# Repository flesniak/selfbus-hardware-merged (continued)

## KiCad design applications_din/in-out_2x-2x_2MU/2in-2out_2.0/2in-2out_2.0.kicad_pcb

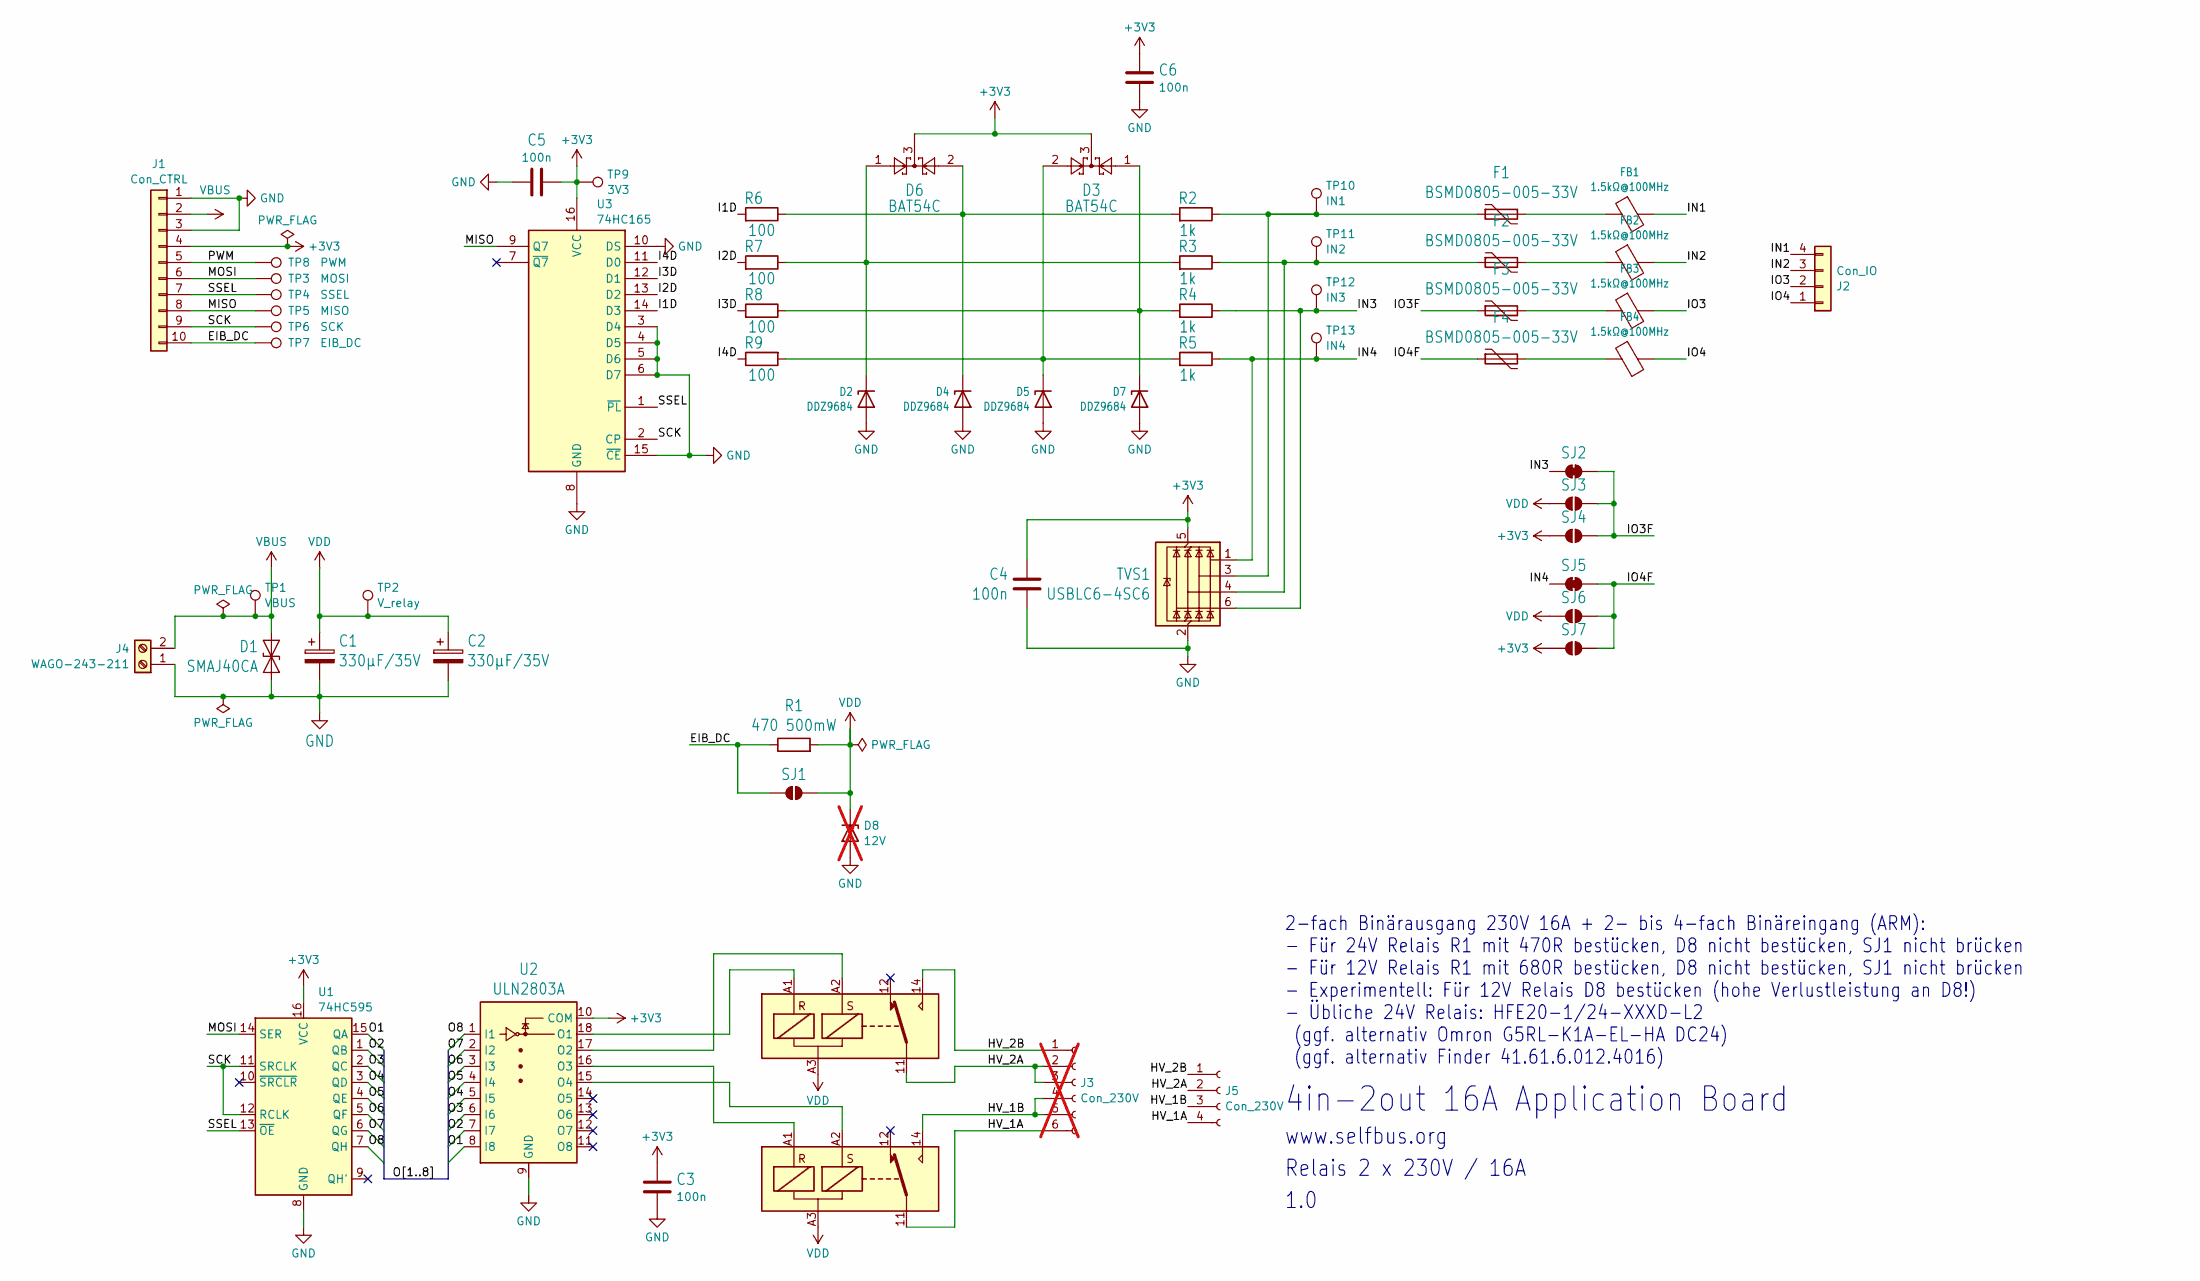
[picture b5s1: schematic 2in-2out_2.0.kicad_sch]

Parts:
C1, C2: 330µF/35V; CP_Radial_D8.0mm_P3.50mm
C3, C4, C5, C6: 100n; C_0805_2012Metric
D1: SMAJ40CA; D_SMA
D2, D4, D5, D7: DDZ9684; D_SOD-123
D3, D6: BAT54C; SOT-23
D8: 12V; D_MiniMELF; not fitted
F1, F2, F3, F4: BSMD0805-005-33V; Fuse_0805_2012Metric
FB1, FB2, FB3, FB4: 1.5kΩ@100MHz; L_0805_2012Metric
J1: Con_CTRL; Molex_KK-254_AE-6410-10A_1x10_P2.54mm_Vertical
J2: Con_IO; TerminalBlock_Phoenix_PTSM-0,5-4-2.5-H-THR_1x04_P2.50mm_Hor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
J3: Con_230V; TerminalBlock_Phoenix_MKDS-3-6-5.08_1x06_P5.08mm_Horizontal; not fitted
J4: WAGO-243-211; W243-211_1x02_P5.75
J5: Con_230V; TerminalBlock_MetzConnect_Type701_RT11L03HGLU_1x04_P6.35mm_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
K1, K2: HFE20-1/24-1HSD-L2; HFE20-GENERIC-COMBO
R1: 470 500mW; R_1206_3216Metric
R2, R3, R4, R5: 1k; R_0805_2012Metric
R6, R7, R8, R9: 100; R_0805_2012Metric
SJ1: RELAY_24V; SolderJumper-2_P1.3mm_Open_Pad1.0x1.5mm
SJ2: IN3_INPUT; SolderJumper-2_P1.3mm_Open_Pad1.0x1.5mm
SJ3: IN3_VDD; SolderJumper-2_P1.3mm_Open_Pad1.0x1.5mm
SJ4: IN3_3V3; SolderJumper-2_P1.3mm_Open_Pad1.0x1.5mm
SJ5: IN4_INPUT; SolderJumper-2_P1.3mm_Open_Pad1.0x1.5mm
SJ6: IN4_VDD; SolderJumper-2_P1.3mm_Open_Pad1.0x1.5mm
SJ7: IN4_3V3; SolderJumper-2_P1.3mm_Open_Pad1.0x1.5mm
TP1: VBUS; TestPoint_Pad_D1.5mm
TP2: V_relay; TestPoint_Pad_D1.5mm
TP3: MOSI; TestPoint_Pad_D1.5mm
TP4: SSEL; TestPoint_Pad_D1.5mm
TP5: MISO; TestPoint_Pad_D1.5mm
TP6: SCK; TestPoint_Pad_D1.5mm
TP7: EIB_DC; TestPoint_Pad_D1.5mm
TP8: PWM; TestPoint_Pad_D1.5mm
TP9: 3V3; TestPoint_Pad_D1.5mm
TP10: IN1; TestPoint_Pad_D1.0mm
TP11: IN2; TestPoint_Pad_D1.0mm
TP12: IN3; TestPoint_Pad_D1.0mm
TP13: IN4; TestPoint_Pad_D1.0mm
TVS1: USBLC6-4SC6; SOT-23-6
U1: 74HC595; SOIC-16_3.9x9.9mm_P1.27mm
U2: ULN2803A; SOIC-18W_7.5x11.6mm_P1.27mm
U3: 74HC165; SO-16_3.9x9.9mm_P1.27mm

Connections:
+3V3: C3.1, C4.2, C5.1, C6.1, D3.3, D6.3, J1.4, SJ4.1 (A), SJ7.1 (A), TP9.1, TVS1.5 (VBUS), U1.16 (VCC), U2.10 (COM), U3.16 (VCC)
/EIB_DC: J1.10, R1.1, SJ1.1 (A), TP7.1
/HV_1A: J3.6, J5.4, K1.11
/HV_1B: J3.4, J3.5, J5.3, K1.14
/HV_2A: J3.2, J3.3, J5.2, K2.11
/HV_2B: J3.1, J5.1, K2.14
/I1D: R6.2, U3.14 (D3)
/I2D: R7.2, U3.13 (D2)
/I3D: R8.2, U3.12 (D1)
/I4D: R9.1, U3.11 (D0)
/IN1: FB1.2, J2.4
/IN2: FB2.2, J2.3
/IN3: R4.1, SJ2.1 (A), TP12.1, TVS1.6 (I/O4)
/IN4: R5.1, SJ5.1 (A), TP13.1, TVS1.1 (I/O1)
/IO3: FB3.2, J2.2
/IO3F: F3.1, SJ2.2 (B), SJ3.2 (B), SJ4.2 (B)
/IO4: FB4.2, J2.1
/IO4F: F4.1, SJ5.2 (B), SJ6.2 (B), SJ7.2 (B)
/MISO: J1.8, TP5.1, U3.9 (Q7)
/MOSI: J1.6, TP3.1, U1.14 (SER)
/O1: U1.15 (QA), U2.8 (I8)
/O2: U1.1 (QB), U2.7 (I7)
/O3: U1.2 (QC), U2.6 (I6)
/O4: U1.3 (QD), U2.5 (I5)
/O5: U1.4 (QE), U2.4 (I4)
/O6: U1.5 (QF), U2.3 (I3)
/O7: U1.6 (QG), U2.2 (I2)
/O8: U1.7 (QH), U2.1 (I1)
/PWM: J1.5, TP8.1
/SCK: J1.9, TP6.1, U1.11 (SRCLK), U1.12 (RCLK), U3.2 (CP)
/SSEL: J1.7, TP4.1, U1.13 (~OE), U3.1 (~PL)
GND: C1.2, C2.2, C3.2, C4.1, C5.2, C6.2, D1.1 (A1), D2.2 (A), D4.2 (A), D5.2 (A), D7.2 (A), D8.2 (A), J1.1, J1.3, J4.1, TVS1.2 (GND), U1.8 (GND), U2.9 (GND), U3.3 (D4), U3.4 (D5), U3.5 (D6), U3.6 (D7), U3.8 (GND), U3.10 (DS), U3.15 (~CE)
unnamed: D2.1 (K), D6.1, R3.2, R7.1
unnamed: D4.1 (K), D6.2, R2.2, R6.1
unnamed: D3.2, D5.1 (K), R5.2, R9.2
unnamed: D3.1, D7.1 (K), R4.2, R8.1
unnamed: F1.2, FB1.1
unnamed: F2.2, FB2.1
unnamed: F3.2, FB3.1
unnamed: F4.2, FB4.1
unnamed: F1.1, R2.1, TP10.1, TVS1.3 (I/O2)
unnamed: F2.1, R3.1, TP11.1, TVS1.4 (I/O3)
unnamed: K2.A1, U2.18 (O1)
unnamed: K2.A2, U2.17 (O2)
unnamed: K1.A1, U2.16 (O3)
unnamed: K1.A2, U2.15 (O4)
VBUS: D1.2 (A2), J1.2, J4.2, TP1.1
VDD: C1.1, C2.1, D8.1 (K), K1.A3, K2.A3, R1.2, SJ1.2 (B), SJ3.1 (A), SJ6.1 (A), TP2.1

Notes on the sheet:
www.selfbus.org
4in-2out 16A Application Board
1.0
2-fach Binärausgang 230V 16A + 2- bis 4-fach Binäreingang (ARM): - Für 24V Relais R1 mit 470R bestücken, D8 nicht bestücken, SJ1 nicht brücken - Für 12V Relais R1 mit 680R bestücken, D8 nicht bestücken, SJ1 nicht brücken - Experimentell: Für 12V Relais D8 bestücken (hohe Verlustleistung an D8!) - Ü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
Relais 2 x 230V / 16A

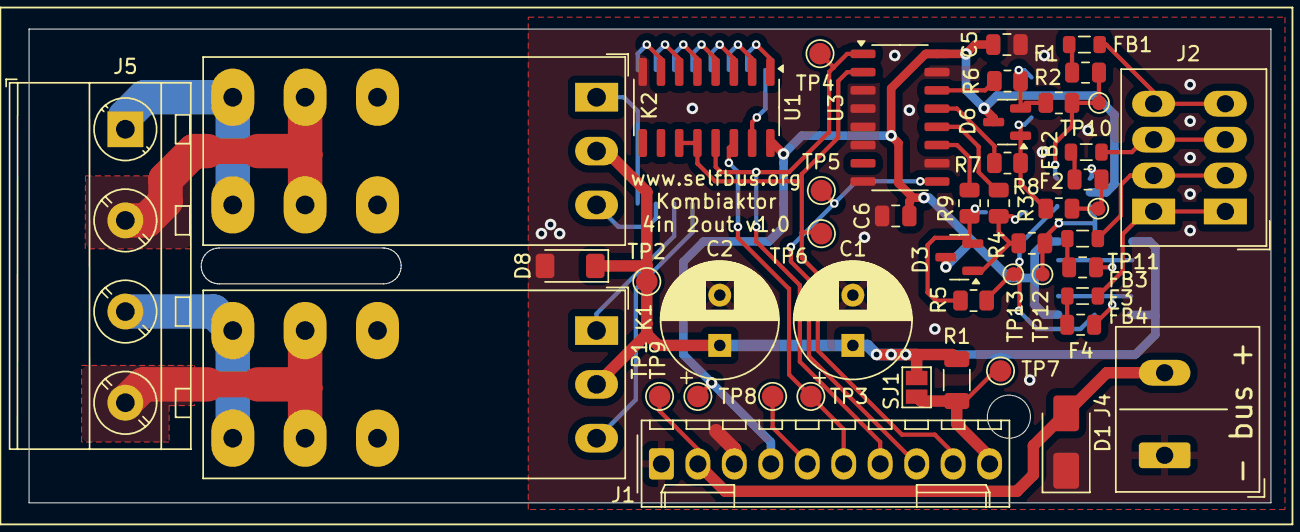
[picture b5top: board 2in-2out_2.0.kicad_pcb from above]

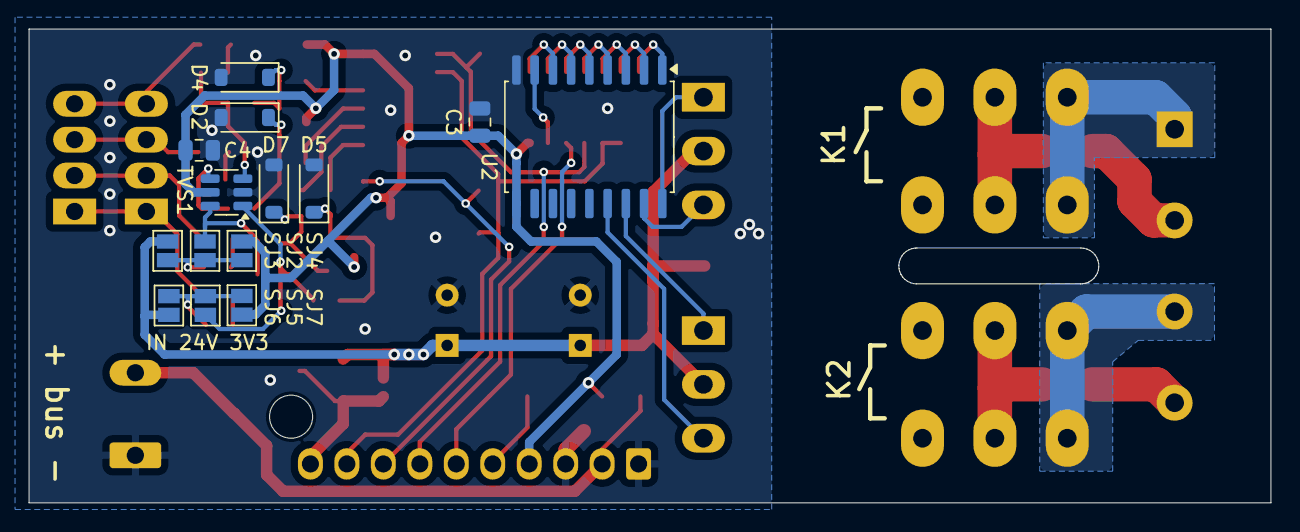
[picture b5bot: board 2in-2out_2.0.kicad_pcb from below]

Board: 2 copper layers, 86.5 x 33.0 mm, 62 parts (14 on the bottom side), 48 nets.

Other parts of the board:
HUT_CNMB_2: BOT; HUT_CNMB_2

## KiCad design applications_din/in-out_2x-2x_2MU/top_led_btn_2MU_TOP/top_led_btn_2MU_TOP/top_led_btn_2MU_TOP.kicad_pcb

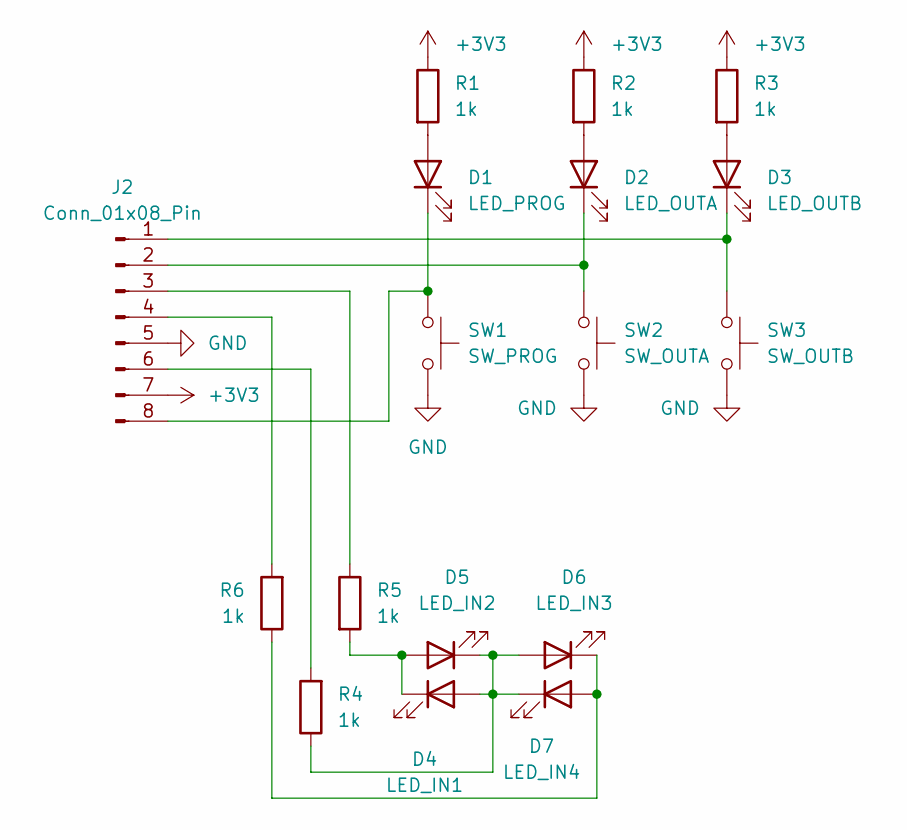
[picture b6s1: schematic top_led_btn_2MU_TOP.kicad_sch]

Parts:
D1: LED_PROG; LED_0805_2012Metric
D2: LED_OUTA; LED_0805_2012Metric
D3: LED_OUTB; LED_0805_2012Metric
D4: LED_IN1; LED_0805_2012Metric
D5: LED_IN2; LED_0805_2012Metric
D6: LED_IN3; LED_0805_2012Metric
D7: LED_IN4; LED_0805_2012Metric
J2: Conn_01x08_Pin; PinHeader_1x08_P2.54mm_Vertical
R1, R2, R3, R4, R5, R6: 1k; R_0805_2012Metric
SW1: SW_PROG; SW_SPST_Omron_B3FS-100xP
SW2: SW_OUTA; SW_SPST_Omron_B3FS-100xP
SW3: SW_OUTB; SW_SPST_Omron_B3FS-100xP

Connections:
+3V3: J2.7, R1.1, R2.1, R3.1
GND: J2.5, SW1.1, SW2.1, SW3.1
unnamed: D1.2 (A), R1.2
unnamed: D1.1 (K), J2.8, SW1.2
unnamed: D2.2 (A), R2.2
unnamed: D2.1 (K), J2.2, SW2.2
unnamed: D3.2 (A), R3.2
unnamed: D3.1 (K), J2.1, SW3.2
unnamed: D4.2 (A), D5.1 (K), D6.2 (A), D7.1 (K), R4.1
unnamed: D4.1 (K), D5.2 (A), R5.2
unnamed: D6.1 (K), D7.2 (A), R6.1
unnamed: J2.3, R5.1
unnamed: J2.4, R6.2
unnamed: J2.6, R4.2

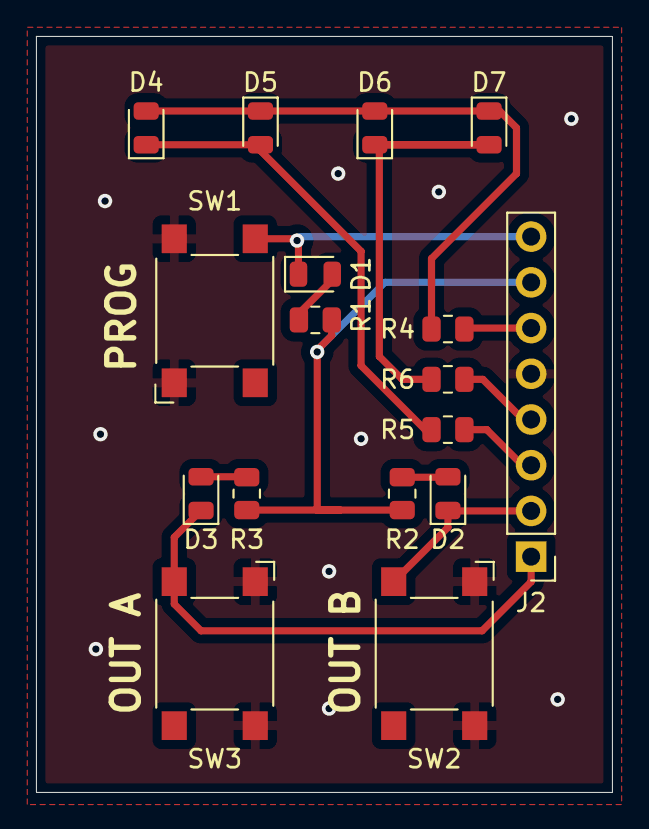
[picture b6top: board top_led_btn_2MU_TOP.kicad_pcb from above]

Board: 2 copper layers, 32.0 x 42.0 mm, 17 parts (0 on the bottom side), 14 nets.

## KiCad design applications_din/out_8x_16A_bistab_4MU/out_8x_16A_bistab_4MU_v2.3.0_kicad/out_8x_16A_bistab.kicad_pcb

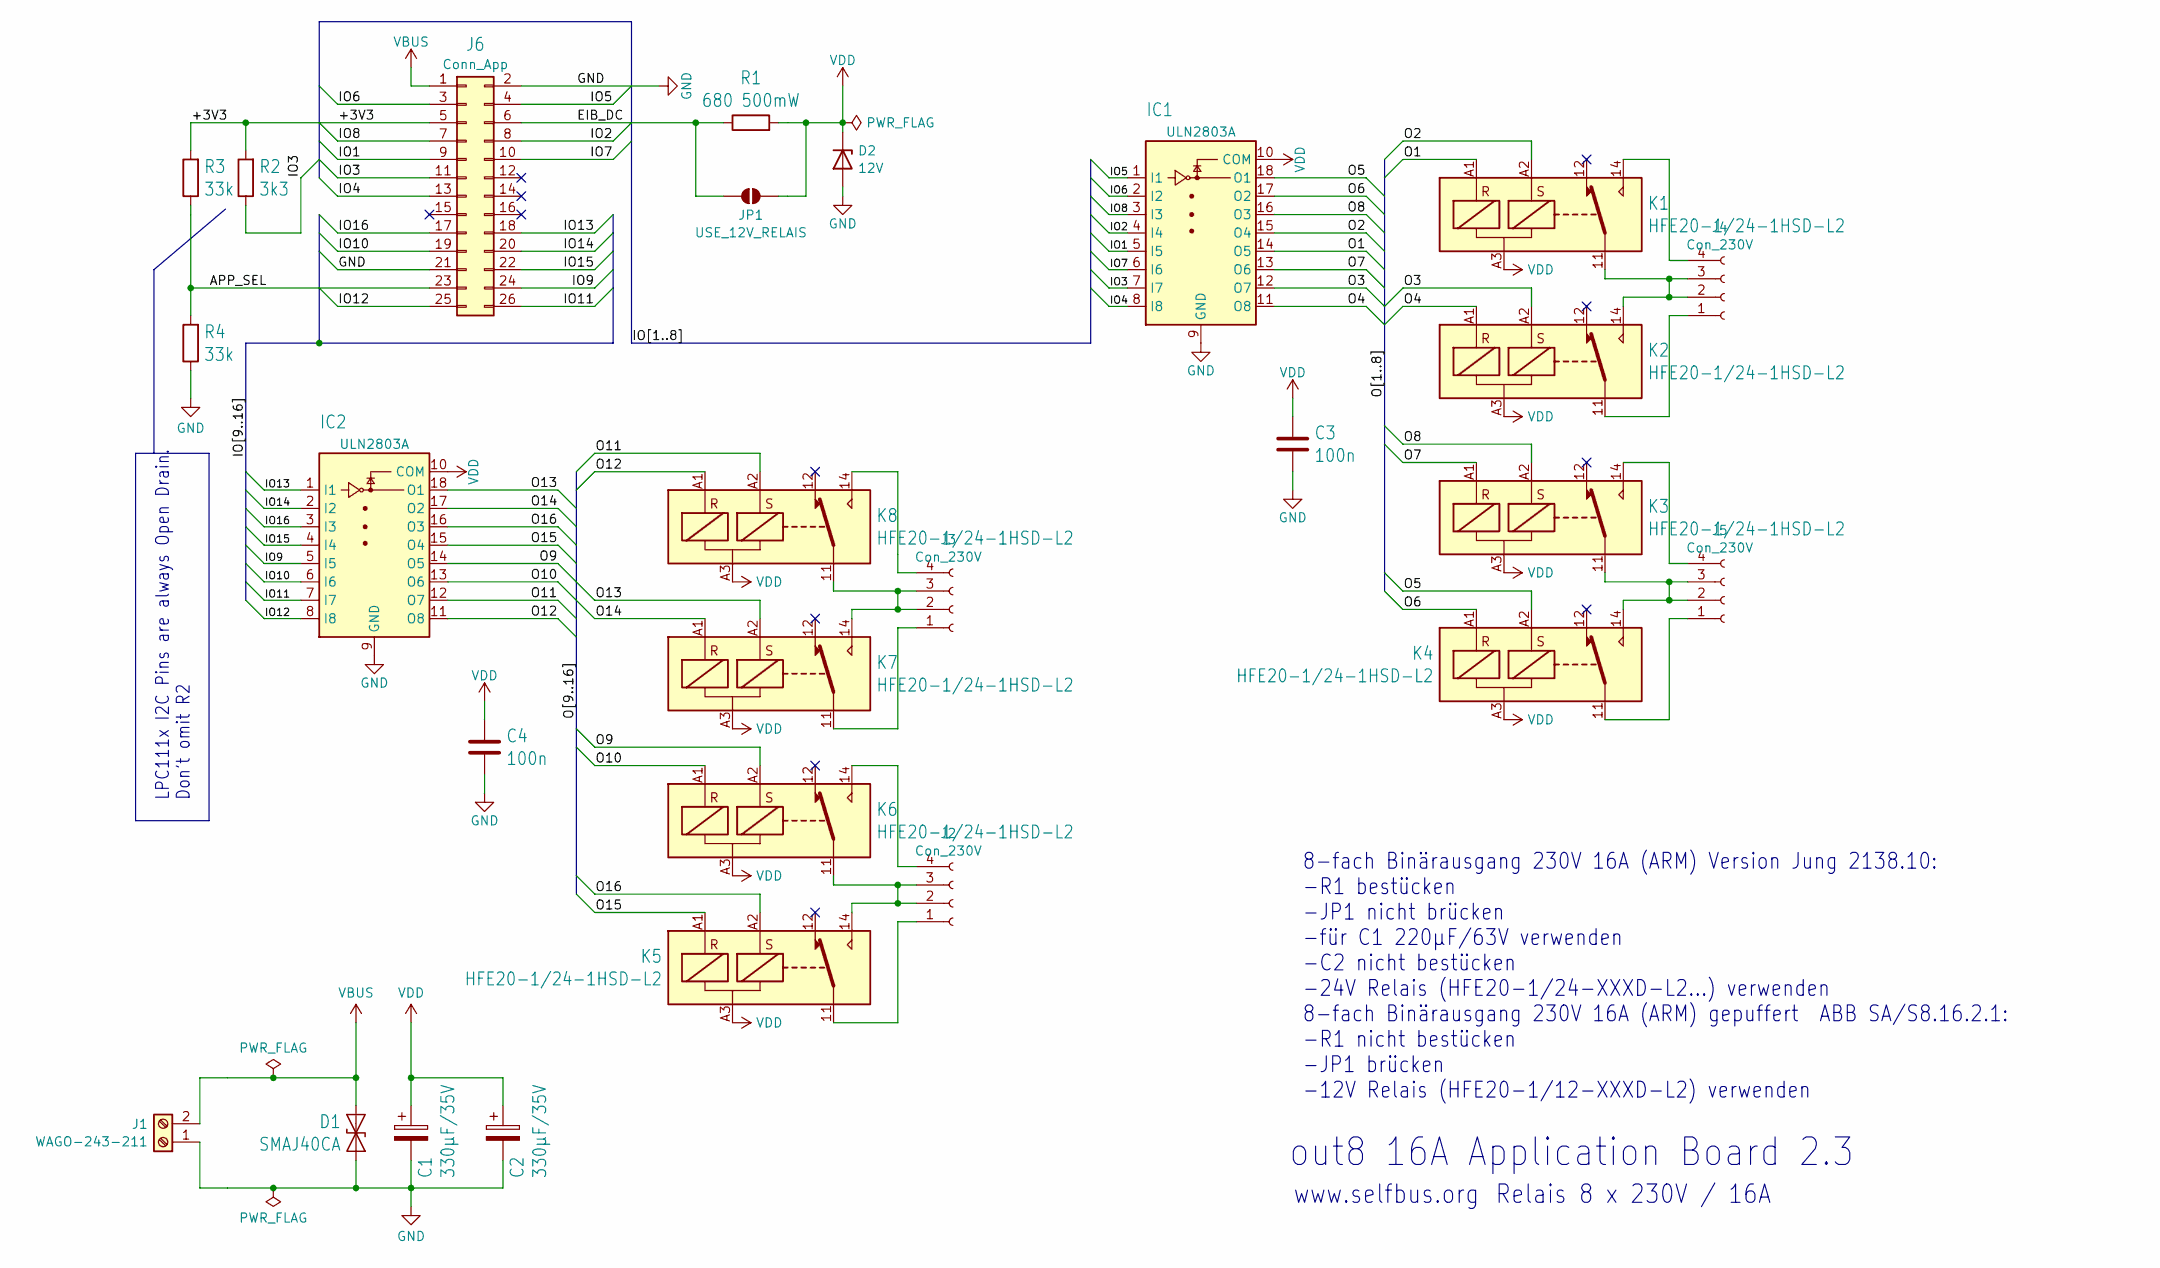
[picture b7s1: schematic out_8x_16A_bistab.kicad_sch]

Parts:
C1, C2: 330µF/35V; CP_Radial_D8.0mm_P3.50mm
C3, C4: 100n; C_0805_2012Metric
D1: SMAJ40CA; D_SMA
D2: 12V; D_MiniMELF
IC1, IC2: ULN2803A; SOIC-18W_7.5x11.6mm_P1.27mm
J1: WAGO-243-211; W243-211_1x02_P5.75
J2, J3, J4, J5: Con_230V; Altech_AK100_1x04_P5.00mm
J6: Conn_App; IDC-Header_2x13_P2.54mm_Vertical_SMD
JP1: USE_12V_RELAIS; SolderJumper-2_P1.3mm_Open_Pad1.0x1.5mm
K1, K2, K3, K4, K5, K6, K7, K8: HFE20-1/24-1HSD-L2; HFE20-1-L2
R1: 680 500mW; R_1206_3216Metric
R2: 3k3; R_0805_2012Metric
R3, R4: 33k; R_0805_2012Metric

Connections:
/+3V3: J6.5, R2.2, R3.2
/APP_SEL: J6.23, R3.1, R4.2
/EIB_DC: J6.6, JP1.1 (A), R1.1
/IO1: IC1.5 (I5), J6.9
/IO2: IC1.4 (I4), J6.8
/IO3: IC1.7 (I7), J6.11, R2.1
/IO4: IC1.8 (I8), J6.13
/IO5: IC1.1 (I1), J6.4
/IO6: IC1.2 (I2), J6.3
/IO7: IC1.6 (I6), J6.10
/IO8: IC1.3 (I3), J6.7
/IO9: IC2.5 (I5), J6.24
/IO10: IC2.6 (I6), J6.19
/IO11: IC2.7 (I7), J6.26
/IO12: IC2.8 (I8), J6.25
/IO13: IC2.1 (I1), J6.18
/IO14: IC2.2 (I2), J6.20
/IO15: IC2.4 (I4), J6.22
/IO16: IC2.3 (I3), J6.17
/O1: IC1.14 (O5), K1.A1
/O2: IC1.15 (O4), K1.A2
/O3: IC1.12 (O7), K2.A2
/O4: IC1.11 (O8), K2.A1
/O5: IC1.18 (O1), K4.A2
/O6: IC1.17 (O2), K4.A1
/O7: IC1.13 (O6), K3.A1
/O8: IC1.16 (O3), K3.A2
/O9: IC2.14 (O5), K6.A2
/O10: IC2.13 (O6), K6.A1
/O11: IC2.12 (O7), K8.A2
/O12: IC2.11 (O8), K8.A1
/O13: IC2.18 (O1), K7.A2
/O14: IC2.17 (O2), K7.A1
/O15: IC2.15 (O4), K5.A1
/O16: IC2.16 (O3), K5.A2
GND: C1.2, C2.2, C3.2, C4.2, D1.1 (A1), D2.2 (A), IC1.9 (GND), IC2.9 (GND), J1.1, J6.2, J6.21, R4.1
unnamed: J2.1, K5.11
unnamed: J2.2, J2.3, K5.14, K6.11
unnamed: J2.4, K6.14
unnamed: J3.1, K7.11
unnamed: J3.2, J3.3, K7.14, K8.11
unnamed: J3.4, K8.14
unnamed: J4.1, K2.11
unnamed: J4.2, J4.3, K1.11, K2.14
unnamed: J4.4, K1.14
unnamed: J5.1, K4.11
unnamed: J5.2, J5.3, K3.11, K4.14
unnamed: J5.4, K3.14
VBUS: D1.2 (A2), J1.2, J6.1
VDD: C1.1, C2.1, C3.1, C4.1, D2.1 (K), IC1.10 (COM), IC2.10 (COM), JP1.2 (B), K1.A3, K2.A3, K3.A3, K4.A3, K5.A3, K6.A3, K7.A3, K8.A3, R1.2

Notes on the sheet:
www.selfbus.org
out8 16A Application Board 2.3
8-fach Binärausgang 230V 16A (ARM) Version Jung 2138.10: -R1 bestücken -JP1 nicht brücken -für C1 220µF/63V verwenden -C2 nicht bestücken -24V Relais (HFE20-1/24-XXXD-L2...) verwenden 8-fach Binärausgang 230V 16A (ARM) gepuffert ABB SA/S8.16.2.1: -R1 nicht bestücken -JP1 brücken -12V Relais (HFE20-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
Relais 8 x 230V / 16A
LPC111x I2C Pins are always Open Drain. Don't omit R2~{}

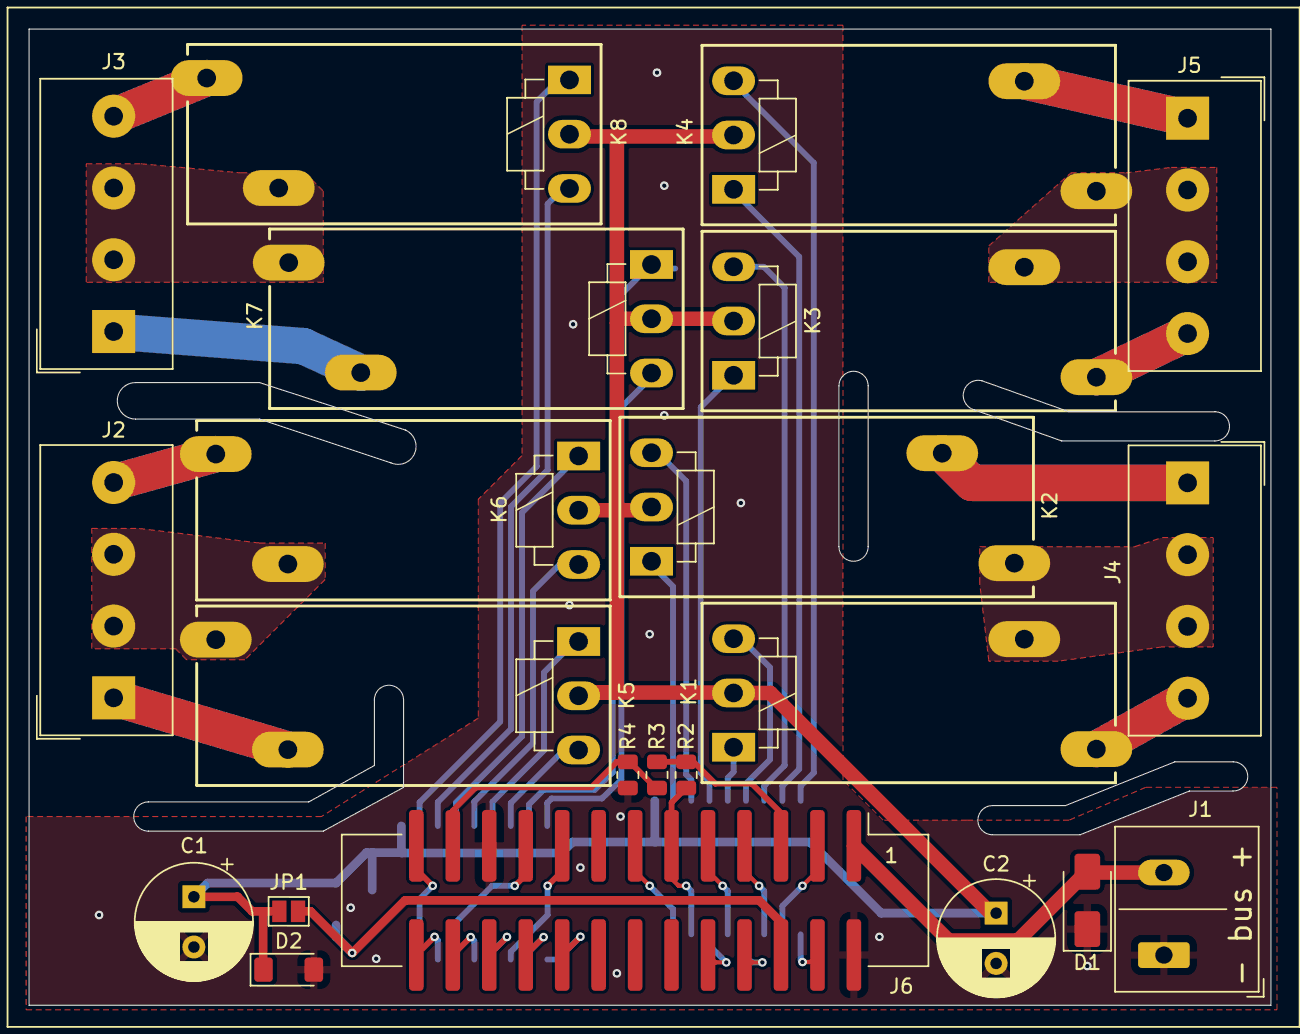
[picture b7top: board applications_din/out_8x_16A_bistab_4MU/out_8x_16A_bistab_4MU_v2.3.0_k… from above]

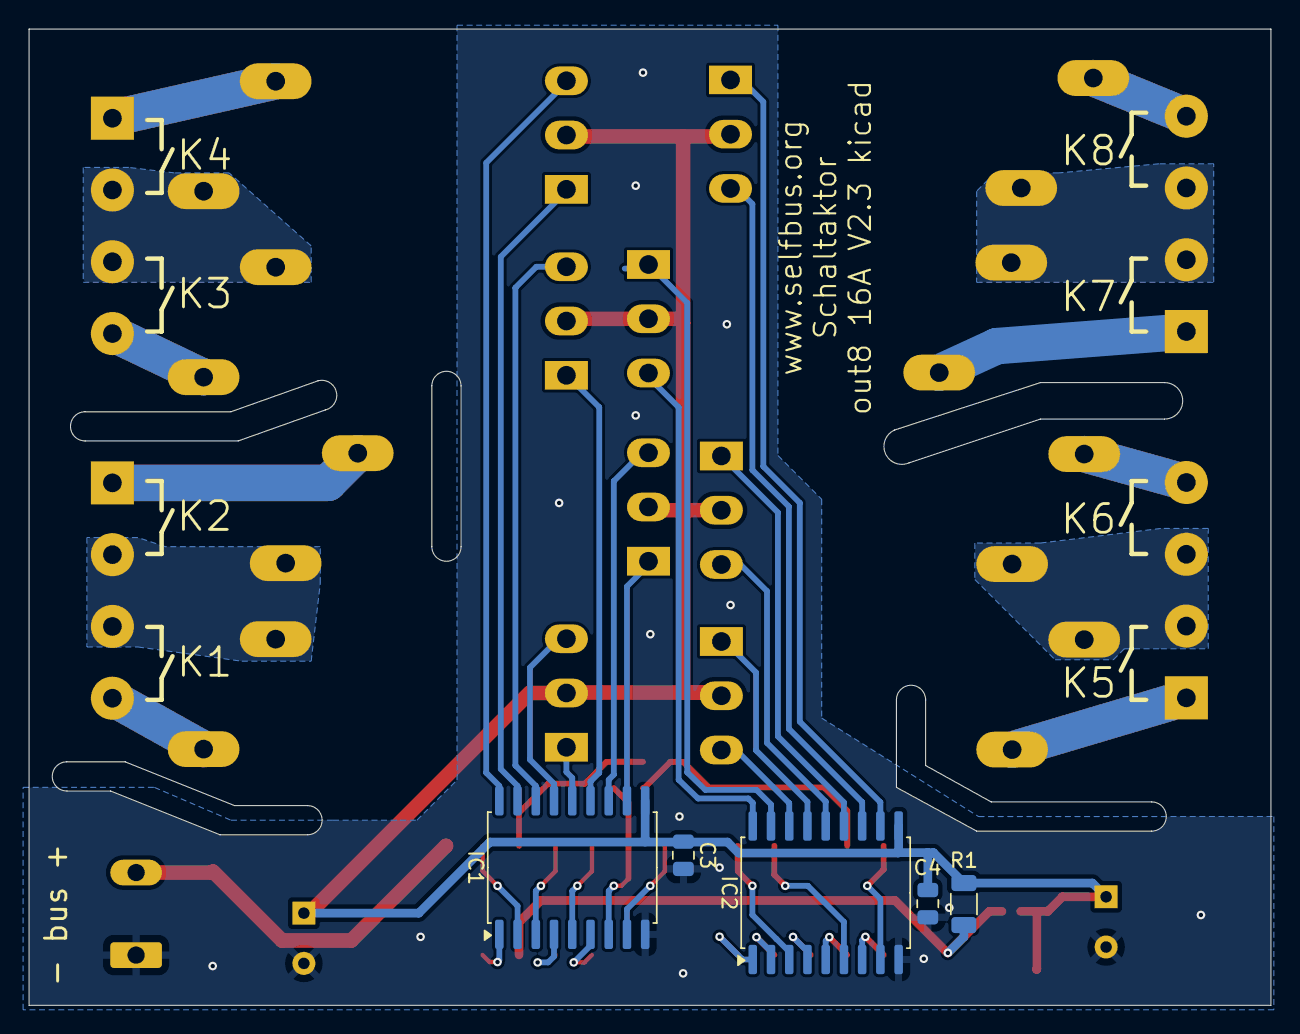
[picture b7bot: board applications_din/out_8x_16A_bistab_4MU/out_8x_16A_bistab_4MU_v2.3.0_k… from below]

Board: 2 copper layers, 86.5 x 68.0 mm, 28 parts (5 on the bottom side), 50 nets.

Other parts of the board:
U$1: HUT_CNMB_4

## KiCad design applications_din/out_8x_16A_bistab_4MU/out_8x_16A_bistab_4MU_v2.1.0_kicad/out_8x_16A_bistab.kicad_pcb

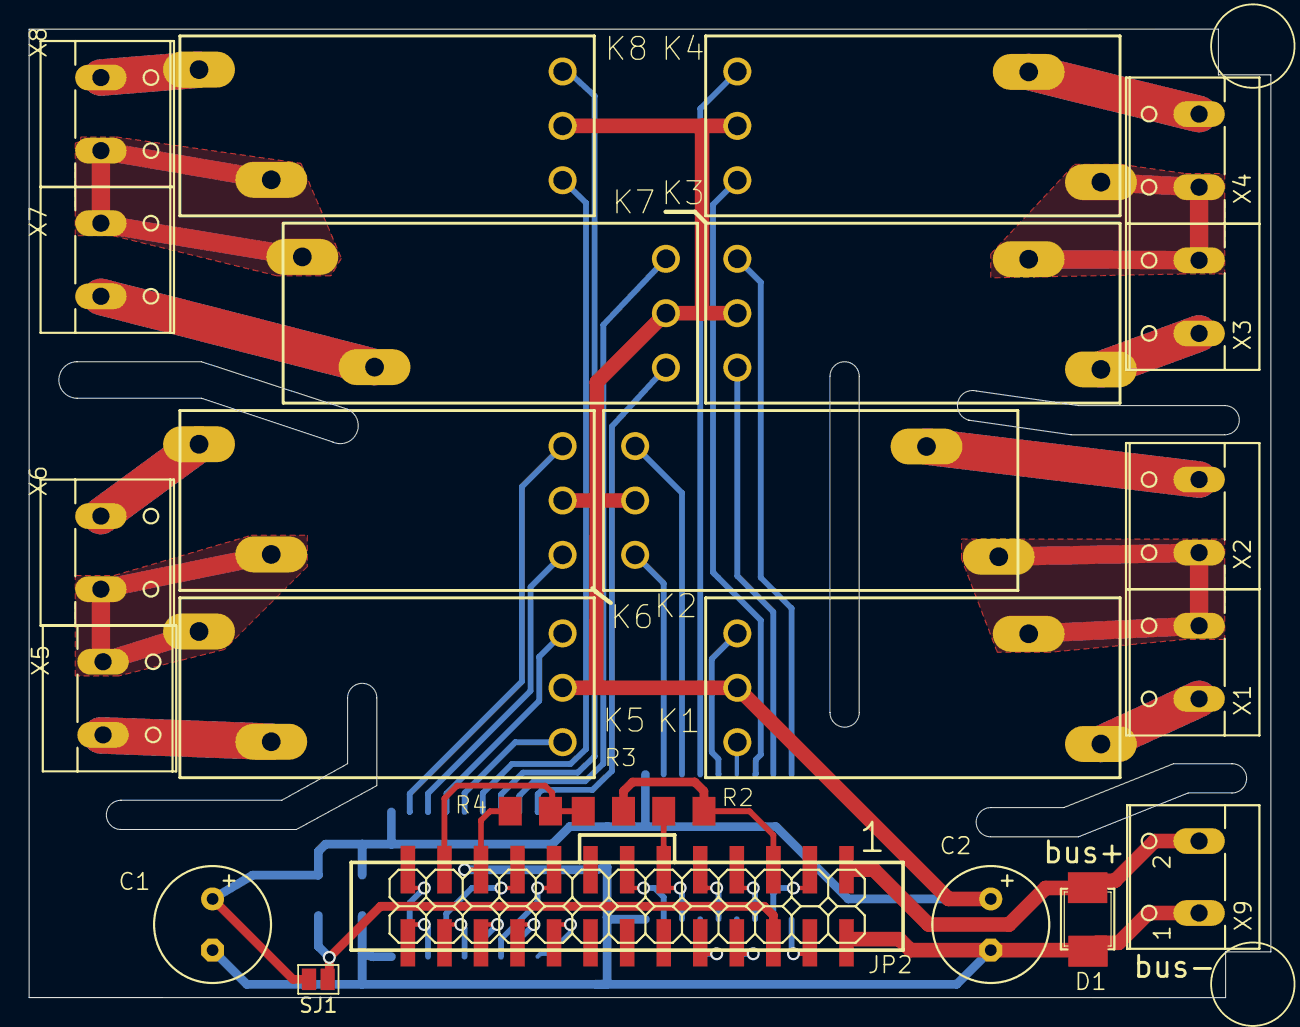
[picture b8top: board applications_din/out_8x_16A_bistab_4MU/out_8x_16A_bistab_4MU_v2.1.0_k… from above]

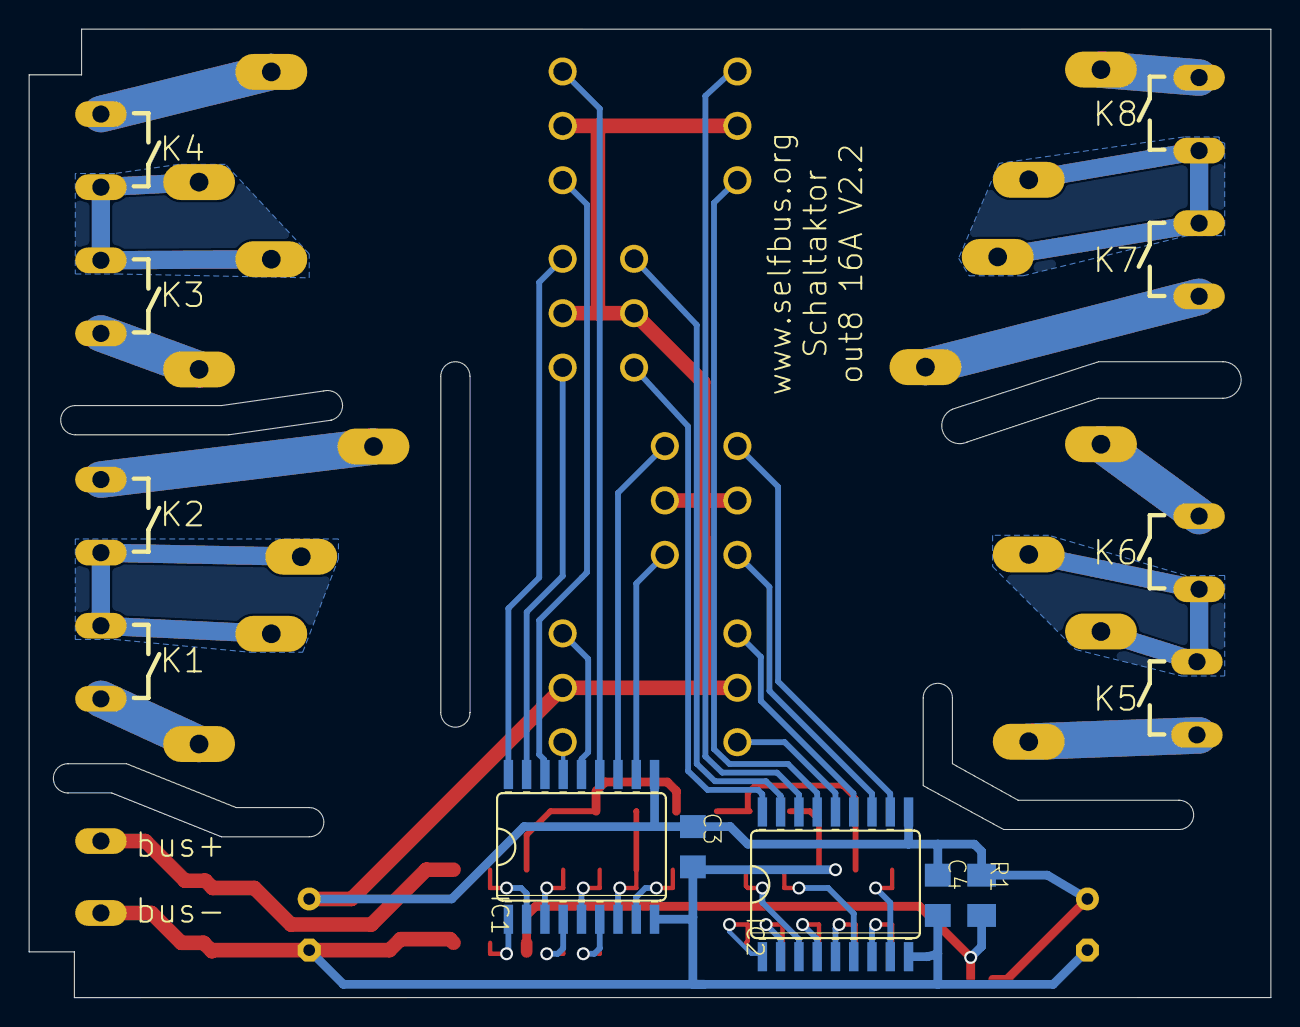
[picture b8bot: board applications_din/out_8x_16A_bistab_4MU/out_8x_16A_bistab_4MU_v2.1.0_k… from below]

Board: 2 copper layers, 86.3 x 67.3 mm, 31 parts (5 on the bottom side), 50 nets.

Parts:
C1, C2: 330µF/35V; E3,5-8
C3, C4: 100n; C1206
D1: SMAJ40CA; SMB
IC1, IC2: ULN2803; SO18W
JP2: A; 2X13SMD
K1, K2, K3, K4, K5, K6, K7, K8: HFE20-1-024-1HD504; HFE20-3-504
R1: 680; M1206
R2: 3k3; M1206
R3, R4: 33k; M1206
SJ1: A; SolderJumper-2_P1.3mm_Open_Pad1.0x1.5mm
U$1: HUT4C-NO-DRILL
X1, X2, X3, X4, X5, X6, X7, X8: W237-02P; W237-132
X9: W237-102

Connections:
+12V: D1.1 (C), JP2.1, X9.2 (KL)
/+3V3: JP2.5, R2.2, R3.2
/APP_SEL: JP2.23, R3.1, R4.2
/EIB_DC: JP2.6, R1.1, SJ1.1
/IO1: IC1.5 (I5), JP2.9
/IO2: IC1.4 (I4), JP2.8
/IO3: IC1.7 (I7), JP2.11, R2.1
/IO4: IC1.8 (I8), JP2.13
/IO5: IC1.1 (I1), JP2.4
/IO6: IC1.2 (I2), JP2.3
/IO7: IC1.6 (I6), JP2.10
/IO8: IC1.3 (I3), JP2.7
/IO9: IC2.5 (I5), JP2.24
/IO10: IC2.6 (I6), JP2.19
/IO11: IC2.7 (I7), JP2.26
/IO12: IC2.8 (I8), JP2.25
/IO13: IC2.1 (I1), JP2.18
/IO14: IC2.2 (I2), JP2.20
/IO15: IC2.4 (I4), JP2.22
/IO16: IC2.3 (I3), JP2.17
/O1: IC1.14 (O5), K1.2 (S+)
/O2: IC1.15 (O4), K1.1 (R+)
/O3: IC1.12 (O7), K2.2 (S+)
/O4: IC1.11 (O8), K2.1 (R+)
/O5: IC1.18 (O1), K3.2 (S+)
/O6: IC1.17 (O2), K3.1 (R+)
/O7: IC1.13 (O6), K4.2 (S+)
/O8: IC1.16 (O3), K4.1 (R+)
/O9: IC2.14 (O5), K5.2 (S+)
/O10: IC2.13 (O6), K5.1 (R+)
/O11: IC2.12 (O7), K6.2 (S+)
/O12: IC2.11 (O8), K6.1 (R+)
/O13: IC2.18 (O1), K7.2 (S+)
/O14: IC2.17 (O2), K7.1 (R+)
/O15: IC2.15 (O4), K8.2 (S+)
/O16: IC2.16 (O3), K8.1 (R+)
GND: C1.-, C2.-, C3.2, C4.2, D1.2 (A), IC1.9 (GND), IC2.9 (GND), JP2.2, JP2.21, R4.1, X9.1 (KL)
unnamed: K1.14B (PA), X1.1 (KL)
unnamed: K1.11A (PB), K2.14B (PA), X1.2 (KL), X2.1 (KL)
unnamed: K2.11A (PB), X2.2 (KL)
unnamed: K3.14B (PA), X3.1 (KL)
unnamed: K3.11A (PB), K4.14B (PA), X3.2 (KL), X4.1 (KL)
unnamed: K4.11A (PB), X4.2 (KL)
unnamed: K5.14B (PA), K6.11A (PB), X5.1 (KL), X6.2 (KL)
unnamed: K5.11A (PB), X5.2 (KL)
unnamed: K6.14B (PA), X6.1 (KL)
unnamed: K7.14B (PA), K8.11A (PB), X7.1 (KL), X8.2 (KL)
unnamed: K7.11A (PB), X7.2 (KL)
unnamed: K8.14B (PA), X8.1 (KL)
VDD: C1.+, C2.+, C3.1, C4.1, IC1.10 (CD+), IC2.10 (CD+), K1.5 (-), K2.5 (-), K3.5 (-), K4.5 (-), K5.5 (-), K6.5 (-), K7.5 (-), K8.5 (-), R1.2, SJ1.2

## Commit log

2024-06-02 update in-out_4x-2x_2MU - final for now
2024-06-02 add global kicad symbol & footprint libs
2024-06-02 out 8x 16A bistab 4MU is now v2.3.0 kicad
2024-06-02 update controller_lpc1115_2MU_v1.04 - final for now
2024-06-02 just all all projects for backup
2024-06-02 add leds_buttons_lpc1115ctrl_2MU
    WIP
2024-06-02 update HFE20 footprint, add BS11, CNMB_4
2024-06-02 add WIP kicad version of controller_lpc1115_2MU_v1.04
2024-06-02 add LPC1115_4TE_TOP - final for now
2024-06-02 fixup! properly rename 4in-2out application & top projects
2024-06-02 add 2in-2out_2.0
    mostly finished
2024-06-02 properly rename 4in-2out application & top projects
2024-06-02 update out_8x_16A_bistab_4MU_v2.3.0_kicad - final for now
2024-06-02 add drill files
2024-06-02 add kicad backup/cache files to gitignore
2024-06-02 rename and move out 8x 16A bistab 2.1 kicad
2024-07-01 add kicad projects for bb_pwr_knx_v-measure and io-16x-fused-fm
    ...imported from eagle
2024-07-01 update all stuff
2024-07-28 add top_led_btn_2MU_TOP
2024-07-28 add controller_lpc1115_2MU_v1.04 gerbers
2024-07-28 add app_out_8x_16A_bistab_4MU_BOT_v2.0.0.kicad_sch
2024-07-28 add app_out_8x_16A_bistab_seperated_4MU_BOT_v2.0.0
2024-07-28 add remaining app_out_8x_16A_bistab_4MU_BOT_v2.0.0
2024-07-28 add top_led_btn_2MU_TOP gerbers - remove!
2024-07-28 drop 2in-2out_2.0/gerber_v2.0
2024-07-28 drop top_led_btn_2MU_TOP/gerber
2024-07-28 drop controller_lpc1115_2MU_v1.04/gerber_v2.0
2024-07-28 clean up controller_lpc1115_2MU_v1.04
2024-07-28 bb_pwr_knx_v-measure final
2024-07-28 io-16x-fused-fm: use micro-match from selfbus library
2024-07-28 bump bb_pwr_knx_v WIP
2024-07-28 fixups for 2MU/4MU controllers - use Seiko oszillator
2024-07-28 bump io-16x-fused-fm - conversion mostly done
2024-07-28 finally standardize selected parts on all boards
2024-07-28 convert io-16x-fused-fm WIP
2024-07-28 move controller_lpc1115_2MU_v1.04 to generic kicad folder
2024-07-28 update LPC1115_4TE_TOP
2024-07-28 update bb_pwr_knx_v-measure
2024-07-28 drop bom+gerber files of io-16x-fused-fm
2024-07-28 final for manufacturing
2024-07-28 update io-16x-fused-fm
2024-07-28 update in-out_4x-2x_2MU
2024-08-18 update xtal caps, eib_in cap+resistor, bus_v resistors
2024-08-18 rename controller_lpc1115_2MU_v1.04 -> lpc1115_2MU_MID
    version 2.01
2024-08-18 gitignore: ignore kicad fp-info-cache
2024-09-02 controllers: reduce osc load, fix DNP for voltage measurement
